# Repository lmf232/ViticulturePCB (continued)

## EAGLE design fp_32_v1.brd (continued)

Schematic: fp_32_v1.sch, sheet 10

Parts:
C41, C71: 0.1uF; C0603
C42: 0.1uF0402; C0402
C72, C73: 2.2uF; C0603
R82, R83: 0 0402; R0402
R97: FERRITE; R0603
U$5: MINISMP_PE44970_THRUHOLE; MINISMP_PE44970_THRU_HOLE
U$46: CVCO55BE-1000-1500_VCO
U$47: PV36W502C01B00_5KTRIMMER
U$48: HEADER_0.1''_1X2

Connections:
+5V: U$47.1; also elsewhere on the board
GND: C41.2, C42.2, C71.2, C72.2, C73.2, U$5.GND1, U$5.GND2, U$5.GND3, U$5.GND4, U$46.P$1 (1_GND), U$46.P$3 (3_GND), U$46.P$4 (4_GND), U$46.P$5 (5_GND), U$46.P$6 (6_GND), U$46.P$7 (7_GND), U$46.P$8 (8_GND), U$46.P$9 (9_GND), U$46.P$11 (11_GND), U$46.P$12 (12_GND), U$46.P$13 (13_GND), U$46.P$15 (15_GND), U$46.P$16 (16_GND), U$47.3, U$48.2; also elsewhere on the board
unnamed: C42.1, U$46.P$2 (2_VT), U$47.2, U$48.1
unnamed: R82.1, R83.2, U$46.P$10 (10_RF_OUT)
unnamed: R83.1, U$5.SIG
unnamed: C41.1, C73.1, R97.1, U$46.P$14 (14_VCC)
RF_SOURCE: R82.2; also elsewhere on the board
V+3V: C71.1, C72.1, R97.2; also elsewhere on the board

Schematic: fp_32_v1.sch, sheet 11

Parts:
C43: 100pF; C0603
C44: 1uF; C0603
C45, C46: 100pF/0402; C0402
R79, R84, R93, R94, R101, R102: 0 0402; R0402
R85: 100nH; R0603
R86: 22; R0805
U$1, U$3: MINISMP_PE44970_THRUHOLE; MINISMP_PE44970_THRU_HOLE
U$40: RF3378_AMPLIFIER; TO243AA/SOT89

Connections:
+5V: C43.1, C44.1, R86.2; also elsewhere on the board
GND: C43.2, C44.2, U$1.GND1, U$1.GND2, U$1.GND3, U$1.GND4, U$3.GND1, U$3.GND2, U$3.GND3, U$3.GND4, U$40.P2 (2_GND), U$40.P4 (4_GND); also elsewhere on the board
unnamed: R94.2, U$1.SIG
unnamed: R84.1, U$3.SIG
unnamed: C45.1, R85.1, U$40.P3 (3_RFOUT)
unnamed: R85.2, R86.1
unnamed: C46.2, U$40.P1 (1_RFIN)
unnamed: C45.2, R93.1, R94.1, R102.1
unnamed: C46.1, R79.2
unnamed: R101.2, R102.2
RF_TX: R93.2; also elsewhere on the board
TX_SWITCH_OUT: R79.1, R84.2, R101.1; also elsewhere on the board

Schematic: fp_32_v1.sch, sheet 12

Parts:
C47, C50, C75: 100pF; C0402
C48: 6.8nH; C0402
C49: 0.1uF0402; C0402
C74: 10pF; C0402
C76: 1000pF; C0402
R87: 0 0402; R0402
R88, R89, R90: 10k0402; R0402
U$42: LTC_5564_ENV_DET; QFN16
U$43: PV36W502C01B00_5KTRIMMER
U$50: HEADER_0.1''_1X2
U$51, U$52: HEADER_0.1''_1X3
U$53: SMA_CONN_SIDE

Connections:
+5V: C74.1, C75.1, C76.1, U$42.P$11 (11_VCCP), U$42.P$12 (12_VCCA), U$42.P$15 (15_VCCRF), U$43.1, U$51.1, U$52.1; also elsewhere on the board
GND: C48.2, C49.2, C50.2, C74.2, C75.2, C76.2, R88.1, R89.1, R90.1, U$42.EP (EP_GND), U$42.P$3 (3_GND), U$42.P$4 (4_GND), U$43.3, U$50.2, U$51.3, U$52.3, U$53.GND1, U$53.GND2; also elsewhere on the board
unnamed: C47.2, U$42.P$1 (1_RFIN)
unnamed: C49.1, R87.2, U$42.P$6 (6_VOUTADJ), U$50.1
unnamed: R87.1, U$43.2
unnamed: C50.1, U$42.P$14 (14_VREF)
unnamed: R88.2, U$42.P$8 (8_G1), U$51.2
unnamed: R89.2, U$42.P$7 (7_G0), U$52.2
unnamed: R90.2, U$42.P$5 (5_LEN)
unnamed: U$42.P$10 (10_VOUT), U$53.CENTER (A)
RX_AMP_OUT: C47.1, C48.1; also elsewhere on the board

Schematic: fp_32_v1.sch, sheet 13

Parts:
C51, C55, C59, C62, C67: 100uF; CAP_POL_RADIAL_8MM_3P5MMPAD
C52, C56, C60, C63, C68: 2.2uF; C0603
C53, C57, C61, C64, C69: 10uF; C1206
C54, C58, C65, C66, C70: 0.1uF; C0603
U$11, U$45, U$55, U$56, U$57, U$58, U$59: DELTRON_BANANA

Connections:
+3V3: C55.PIN+, C56.1, C57.1, C58.1, U$57.A, U$57.B; also elsewhere on the board
+5V: C51.PIN+, C52.1, C53.1, C54.1, U$56.A, U$56.B; also elsewhere on the board
-5V: C62.PIN-, C63.2, C64.2, C65.2, U$45.A, U$45.B; also elsewhere on the board
GND: C51.PIN-, C52.2, C53.2, C54.2, C55.PIN-, C56.2, C57.2, C58.2, C59.PIN-, C60.2, C61.2, C62.PIN+, C63.1, C64.1, C65.1, C66.2, C67.PIN-, C68.2, C69.2, C70.2, U$11.A, U$11.B, U$55.A, U$55.B; also elsewhere on the board
V+3V: C67.PIN+, C68.1, C69.1, C70.1, U$59.A, U$59.B; also elsewhere on the board
V_2P5: C59.PIN+, C60.1, C61.1, C66.1, U$58.A, U$58.B; also elsewhere on the board

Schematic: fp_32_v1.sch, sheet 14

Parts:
U$4: VHDCI_DIGILENT_V1; VHCDI_DIGILENT_V1

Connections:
A0_3_1: U$4.P29; also elsewhere on the board
A1_3_1: U$4.P31; also elsewhere on the board
CDRIVE: U$4.P34; also elsewhere on the board
CS1: U$4.P35; also elsewhere on the board
CS2: U$4.P37; also elsewhere on the board
CS3: U$4.P38; also elsewhere on the board
CS4: U$4.P40; also elsewhere on the board
CS5: U$4.P41; also elsewhere on the board
CS6: U$4.P43; also elsewhere on the board
CS7: U$4.P44; also elsewhere on the board
CS8: U$4.P46; also elsewhere on the board
CS9: U$4.P47; also elsewhere on the board
ENB_3_1: U$4.P28; also elsewhere on the board
F_A0_1A: U$4.P7; also elsewhere on the board
F_A0_1B: U$4.P12; also elsewhere on the board
F_A0_2: U$4.P23; also elsewhere on the board
F_A1_1A: U$4.P9; also elsewhere on the board
F_A1_1B: U$4.P13; also elsewhere on the board
F_A1_2: U$4.P25; also elsewhere on the board
F_ENB_1A: U$4.P6; also elsewhere on the board
F_ENB_1B: U$4.P10; also elsewhere on the board
F_ENB_2: U$4.P22; also elsewhere on the board
GND: U$4.G1, U$4.G2, U$4.G3, U$4.G4, U$4.P2, U$4.P5, U$4.P8, U$4.P11, U$4.P14, U$4.P21, U$4.P24, U$4.P27, U$4.P30, U$4.P33, U$4.P36, U$4.P39, U$4.P42, U$4.P45, U$4.P48, U$4.P55, U$4.P58, U$4.P61, U$4.P64, U$4.P67; also elsewhere on the board
MOSI: U$4.P3; also elsewhere on the board
NC1: U$4.P26
NC5: U$4.P32
NC6: U$4.P66
NC7: U$4.P65
NC8: U$4.P63
NC9: U$4.P62
NC10: U$4.P60
NC11: U$4.P59
NC12: U$4.P57
NC13: U$4.P56
RESETB: U$4.P1; also elsewhere on the board
SCK: U$4.P4; also elsewhere on the board
TX_PULSE: U$4.P68; also elsewhere on the board

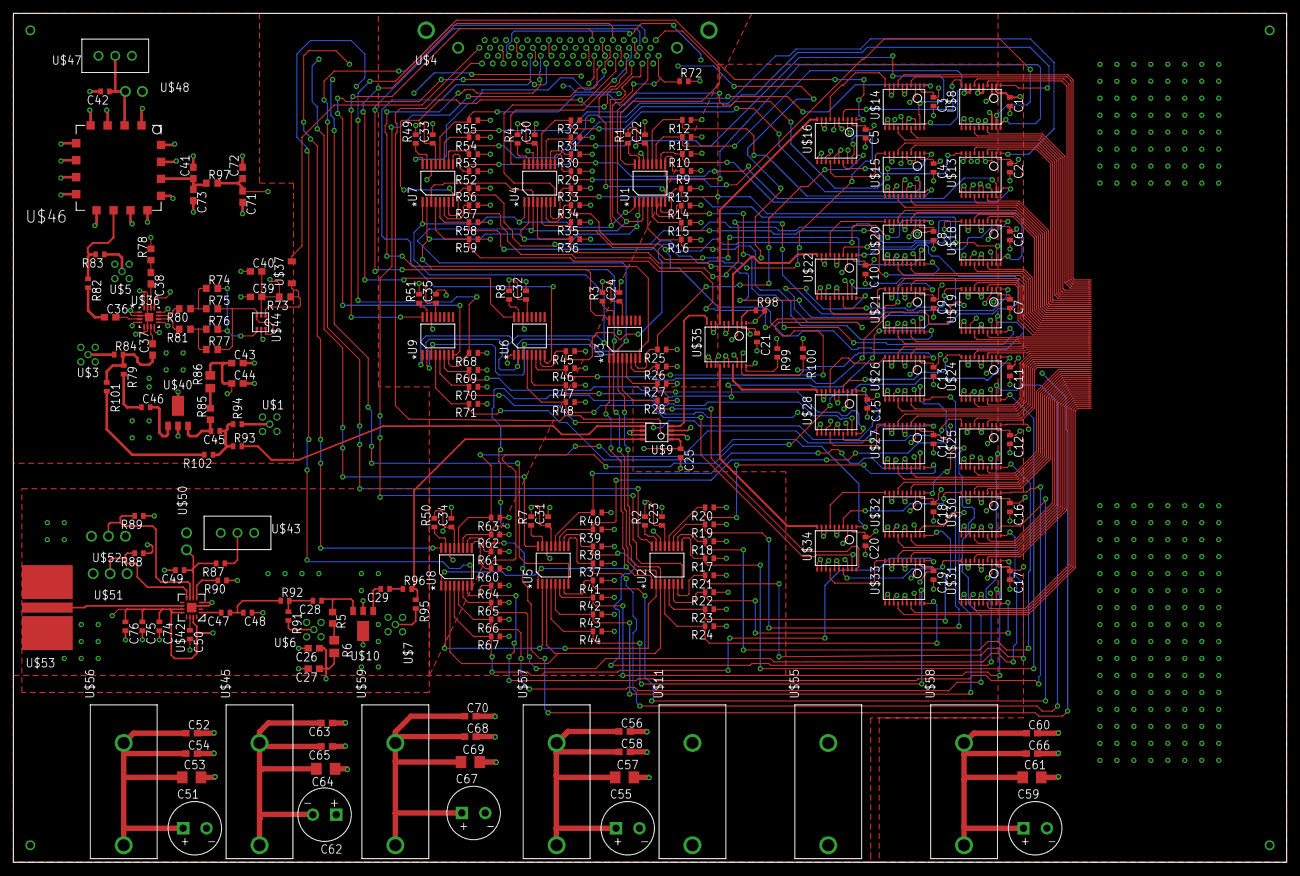
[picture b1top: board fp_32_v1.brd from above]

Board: 4 copper layers, 190.5 x 127.0 mm, 240 parts (0 on the bottom side), 229 nets.

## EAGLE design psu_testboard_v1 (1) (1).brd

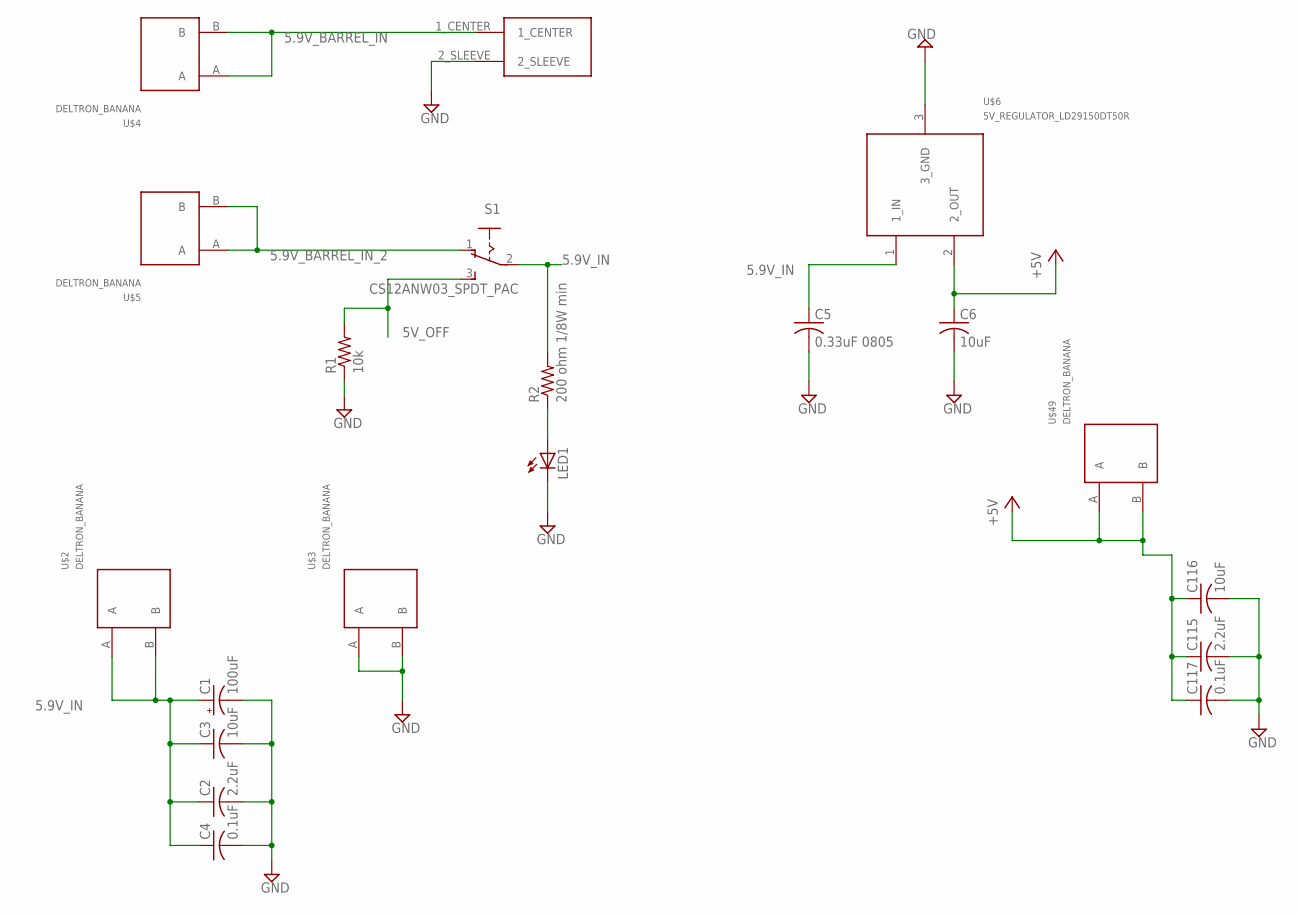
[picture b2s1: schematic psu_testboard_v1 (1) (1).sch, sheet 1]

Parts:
C1: 100uF; CAP_POL_RADIAL_8MM_3P5MMPAD
C2, C115: 2.2uF; C0603
C3, C116: 10uF; C1206
C4, C117: 0.1uF; C0603
C5: 0.33uF 0805; C0805
C6: 10uF; 5MM_SMT_ELECTROLYTICCAP_PANASONIC
LED1: LED3MM
R1: 10k; R0603
R2: 200 ohm 1/8W min; R0603
S1: CS12ANW03_SPDT_PAC; CS12ANW03_NKK_SPDT_SLIDESWITCH_PAC
U$1: BARREL_JACK_PJ-037A
U$2, U$3, U$4, U$5, U$49: DELTRON_BANANA
U$6: 5V_REGULATOR_LD29150DT50R; DPAK

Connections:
5.9V_BARREL_IN: U$1.1_CENTER, U$4.A, U$4.B
5.9V_BARREL_IN_2: S1.1, U$5.A, U$5.B
5.9V_IN: C1.PIN+, C2.1, C3.1, C4.1, C5.1, R2.2, S1.2, U$2.A, U$2.B, U$6.1 (1_IN); also elsewhere on the board
5V_OFF: R1.2, S1.3
+5V: C6.1+ (1), C115.1, C116.1, C117.1, U$6.2 (2_OUT), U$49.A, U$49.B; also elsewhere on the board
GND: C1.PIN-, C2.2, C3.2, C4.2, C5.2, C6.2- (2), C115.2, C116.2, C117.2, LED1.K (C), R1.1, U$1.2_SLEEVE, U$3.A, U$3.B, U$6.3 (3_GND); also elsewhere on the board
unnamed: LED1.A, R2.1

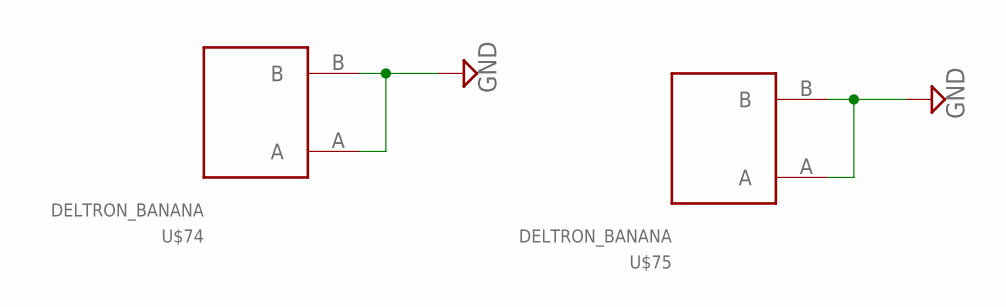
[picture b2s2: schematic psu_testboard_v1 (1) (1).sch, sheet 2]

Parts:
U$74, U$75: DELTRON_BANANA

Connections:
GND: U$74.A, U$74.B, U$75.A, U$75.B; also elsewhere on the board

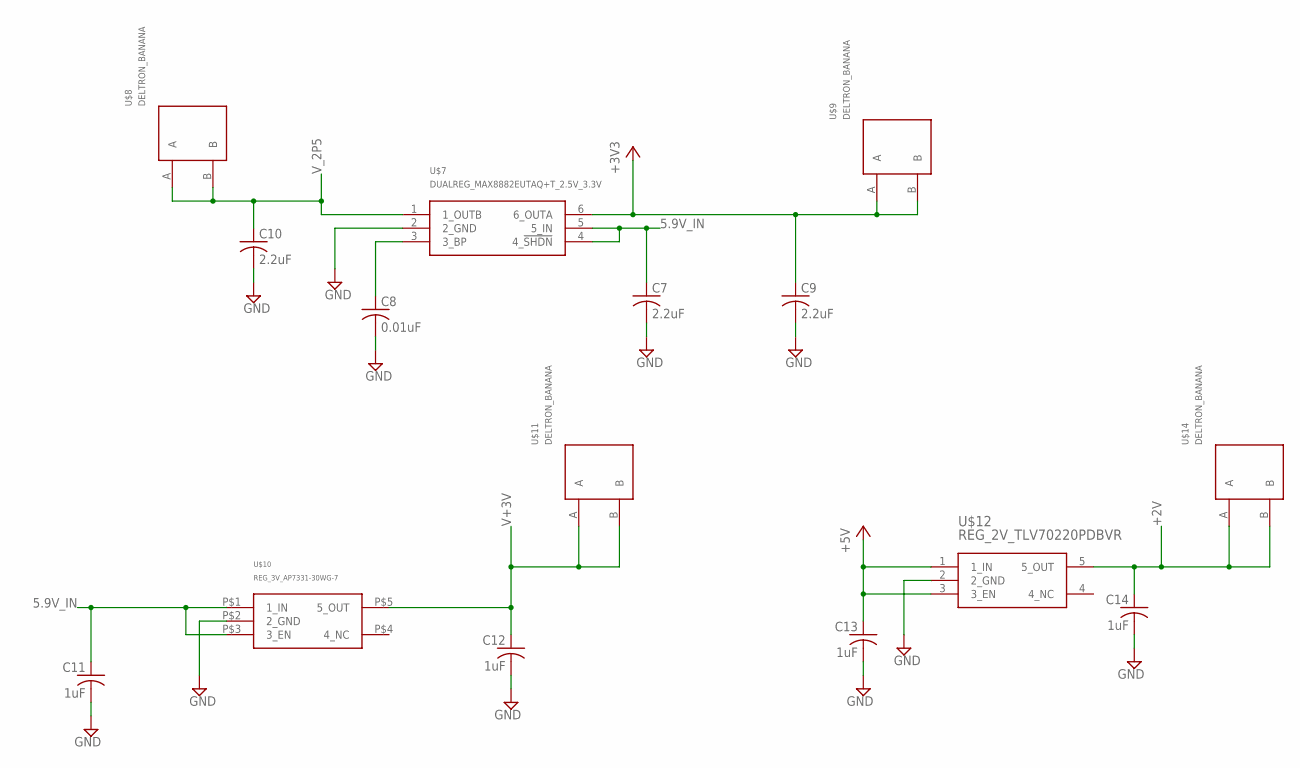
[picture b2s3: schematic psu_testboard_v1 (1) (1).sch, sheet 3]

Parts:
C7, C9, C10: 2.2uF; C0603
C8: 0.01uF; C0603
C11, C12, C13, C14: 1uF; C0603
U$7: DUALREG_MAX8882EUTAQ+T_2.5V_3.3V; SOT23-6
U$8, U$9, U$11, U$14: DELTRON_BANANA
U$10: REG_3V_AP7331-30WG-7; SOT-25
U$12: REG_2V_TLV70220PDBVR; SOT23-5

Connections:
5.9V_IN: C7.1, C11.1, U$7.4 (4_!SHDN), U$7.5 (5_IN), U$10.P$1 (1_IN), U$10.P$3 (3_EN); also elsewhere on the board
+2V: C14.1, U$12.5 (5_OUT), U$14.A, U$14.B
+3V3: C9.1, U$7.6 (6_OUTA), U$9.A, U$9.B; also elsewhere on the board
+5V: C13.1, U$12.1 (1_IN), U$12.3 (3_EN); also elsewhere on the board
GND: C7.2, C8.2, C9.2, C10.2, C11.2, C12.2, C13.2, C14.2, U$7.2 (2_GND), U$10.P$2 (2_GND), U$12.2 (2_GND); also elsewhere on the board
unnamed: C8.1, U$7.3 (3_BP)
V+3V: C12.1, U$10.P$5 (5_OUT), U$11.A, U$11.B
V_2P5: C10.1, U$7.1 (1_OUTB), U$8.A, U$8.B

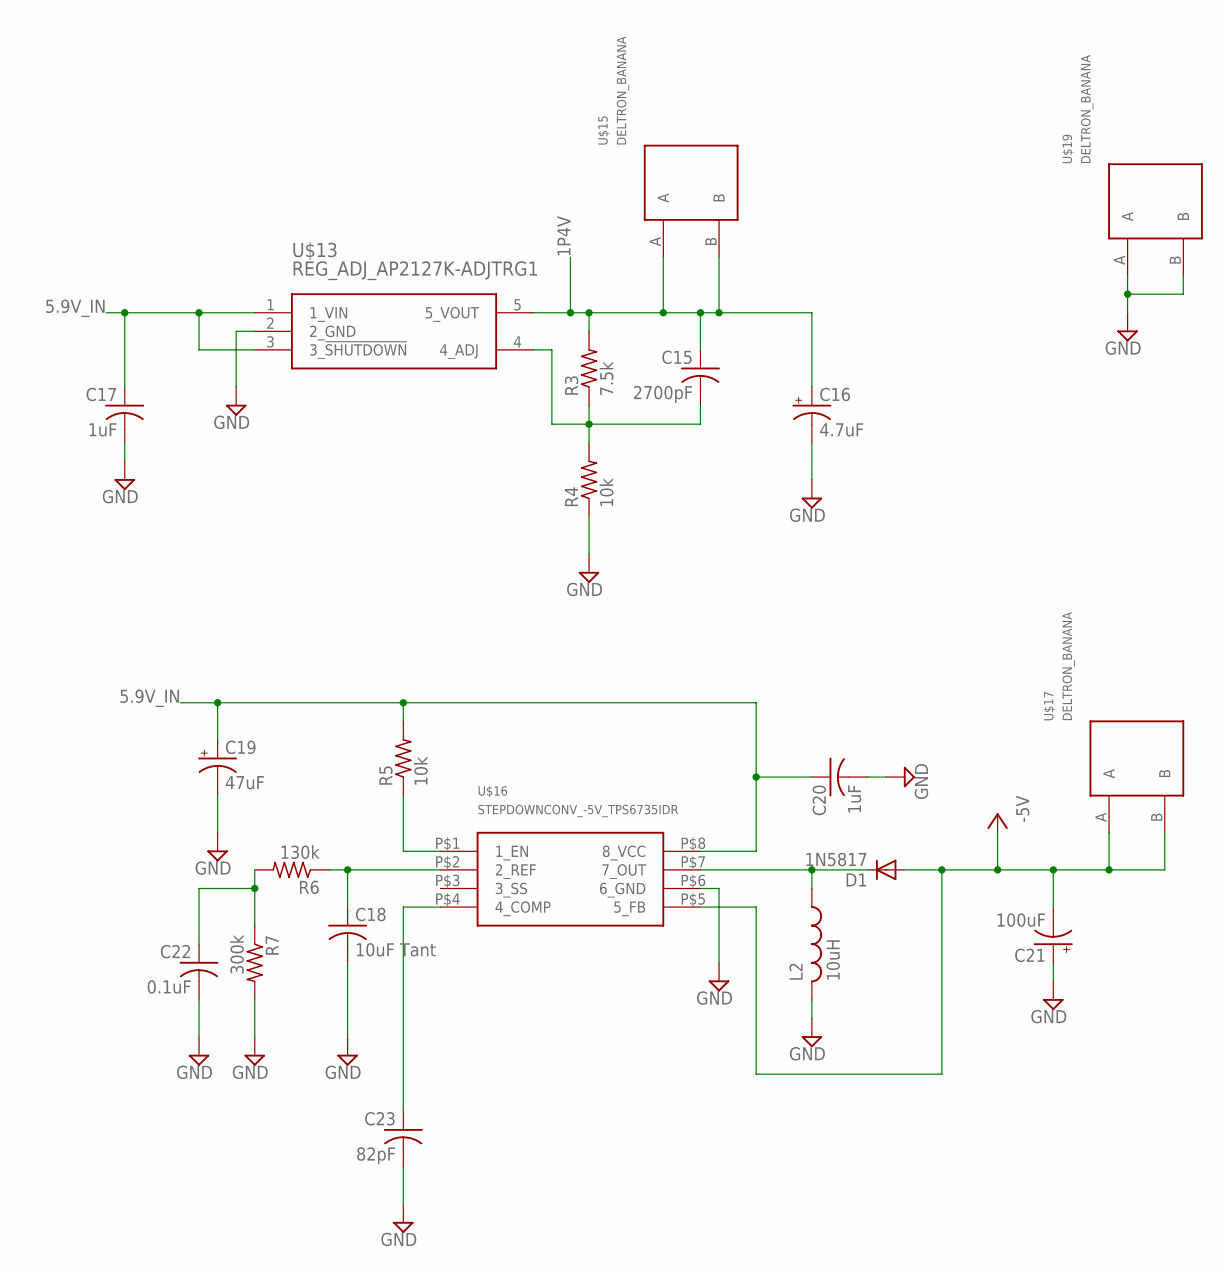
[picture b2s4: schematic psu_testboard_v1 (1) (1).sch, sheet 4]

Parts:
C15: 2700pF; C0603
C16: 4.7uF; E2,5RE
C17, C20: 1uF; C0603
C18: 10uF Tant; C1206
C19: 47uF; E5-10,5
C21: 100uF; E2,5-7
C22: 0.1uF; C0603
C23: 82pF; C0603
D1: 1N5817; DIODE-1N4148
L2: 10uH; COILCRAFT_POWERIND_DO1608C-103MLB
R3: 7.5k; R0603
R4, R5: 10k; R0603
R6: 130k; R0603
R7: 300k; R0603
U$13: REG_ADJ_AP2127K-ADJTRG1; SOT23-5
U$15, U$17, U$19: DELTRON_BANANA
U$16: STEPDOWNCONV_-5V_TPS6735IDR; SOIC8

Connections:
1P4V: C15.1, C16.+, R3.2, U$13.5 (5_VOUT), U$15.A, U$15.B
5.9V_IN: C17.1, C19.+, C20.1, R5.2, U$13.1 (1_VIN), U$13.3 (3_!SHUTDOWN), U$16.P$8 (8_VCC); also elsewhere on the board
-5V: C21.-, D1.A, U$16.P$5 (5_FB), U$17.A, U$17.B; also elsewhere on the board
GND: C16.-, C17.2, C18.2, C19.-, C20.2, C21.+, C22.2, C23.2, L2.P$2 (2), R4.1, R7.2, U$13.2 (2_GND), U$16.P$6 (6_GND), U$19.A, U$19.B; also elsewhere on the board
unnamed: D1.C, L2.P$1 (1), U$16.P$7 (7_OUT)
unnamed: C15.2, R3.1, R4.2, U$13.4 (4_ADJ)
unnamed: R5.1, U$16.P$1 (1_EN)
unnamed: C22.1, R6.2, R7.1
unnamed: C18.1, R6.1, U$16.P$2 (2_REF)
unnamed: C23.1, U$16.P$4 (4_COMP)

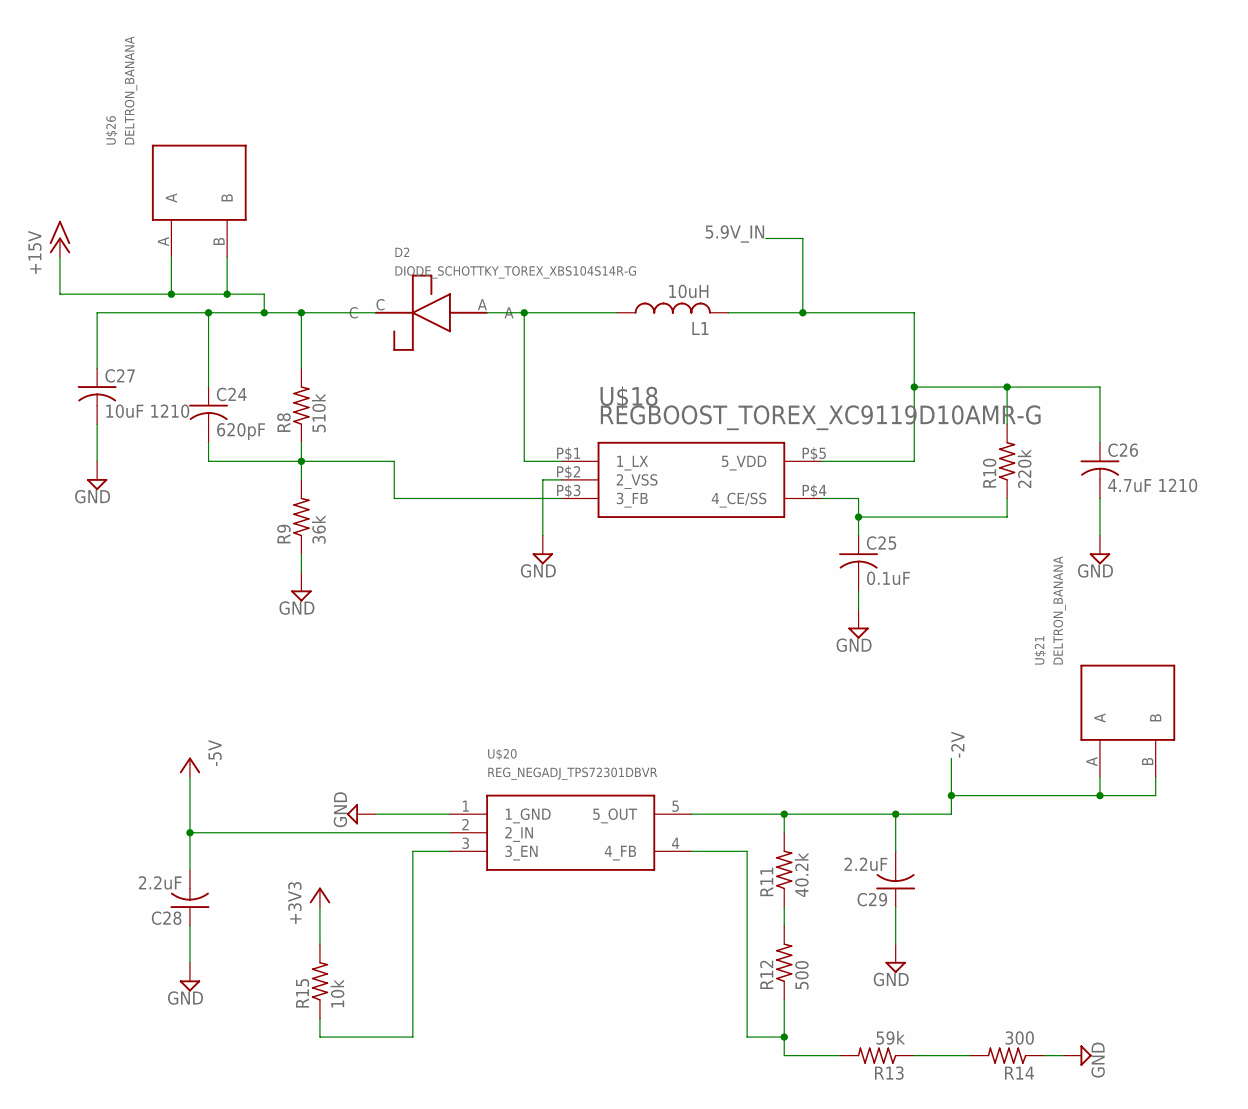
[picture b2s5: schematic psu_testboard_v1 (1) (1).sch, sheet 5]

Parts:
C24: 620pF; C0603
C25: 0.1uF; C0603
C26: 4.7uF 1210; C1210
C27: 10uF 1210; C1210
C28, C29: 2.2uF; C0603
D2: DIODE_SCHOTTKY_TOREX_XBS104S14R-G; SOD-123A
L1: 10uH; SUMIDA_INDUCTOR_CDRH4D18CNP-100PC
R8: 510k; R0603
R9: 36k; R0603
R10: 220k; R0603
R11: 40.2k; R0603
R12: 500; R0603
R13: 59k; R0603
R14: 300; R0603
R15: 10k; R0603
U$18: REGBOOST_TOREX_XC9119D10AMR-G; SOT25-5
U$20: REG_NEGADJ_TPS72301DBVR; SOT23-5
U$21, U$26: DELTRON_BANANA

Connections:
5.9V_IN: C26.1, L1.P$2 (2), R10.2, U$18.P$5 (5_VDD); also elsewhere on the board
+3V3: R15.2; also elsewhere on the board
+15V: C24.1, C27.1, D2.C, R8.2, U$26.A, U$26.B
-2V: C29.2, R11.2, U$20.5 (5_OUT), U$21.A, U$21.B
-5V: C28.2, U$20.2 (2_IN); also elsewhere on the board
GND: C25.2, C26.2, C27.2, C28.1, C29.1, R9.1, R14.1, U$18.P$2 (2_VSS), U$20.1 (1_GND); also elsewhere on the board
unnamed: R13.1, R14.2
unnamed: D2.A, L1.P$1 (1), U$18.P$1 (1_LX)
unnamed: C24.2, R8.1, R9.2, U$18.P$3 (3_FB)
unnamed: R12.1, R13.2, U$20.4 (4_FB)
unnamed: C25.1, R10.1, U$18.P$4 (4_CE/SS)
unnamed: R11.1, R12.2
unnamed: R15.1, U$20.3 (3_EN)

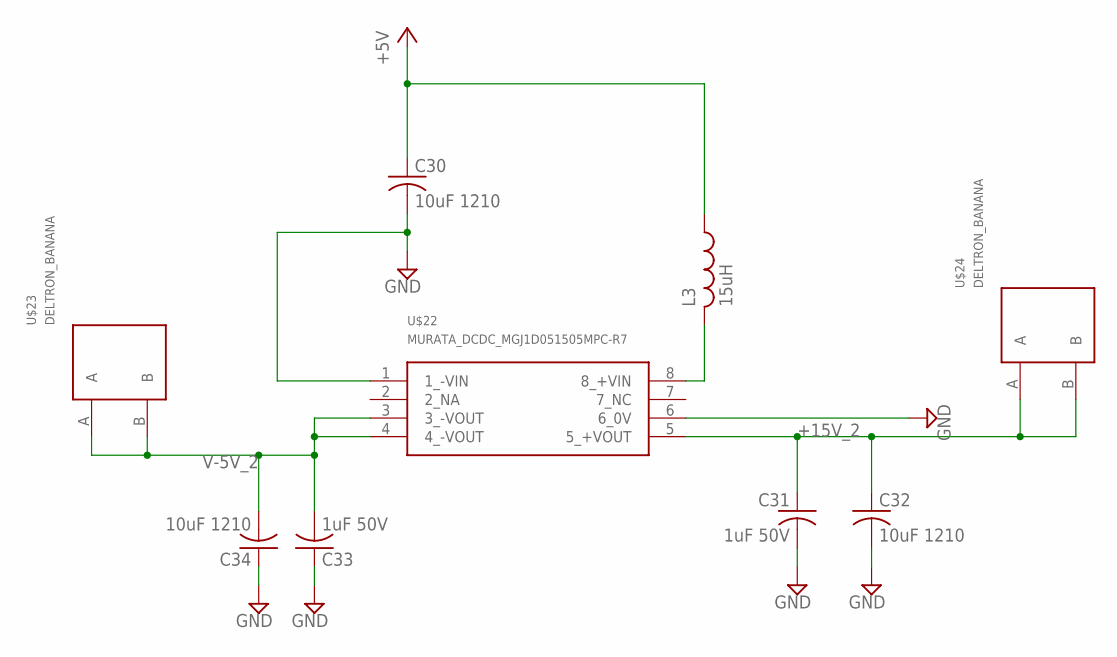
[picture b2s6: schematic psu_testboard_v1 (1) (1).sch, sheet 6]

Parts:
C30, C32, C34: 10uF 1210; C1210
C31, C33: 1uF 50V; C0603
L3: 15uH; 0207/5V
U$22: MURATA_DCDC_MGJ1D051505MPC-R7
U$23, U$24: DELTRON_BANANA

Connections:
+5V: C30.1, L3.1; also elsewhere on the board
+15V_2: C31.1, C32.1, U$22.5 (5_+VOUT), U$24.A, U$24.B
GND: C30.2, C31.2, C32.2, C33.1, C34.1, U$22.1 (1_-VIN), U$22.6 (6_0V); also elsewhere on the board
unnamed: L3.2, U$22.8 (8_+VIN)
V-5V_2: C33.2, C34.2, U$22.3 (3_-VOUT), U$22.4 (4_-VOUT), U$23.A, U$23.B

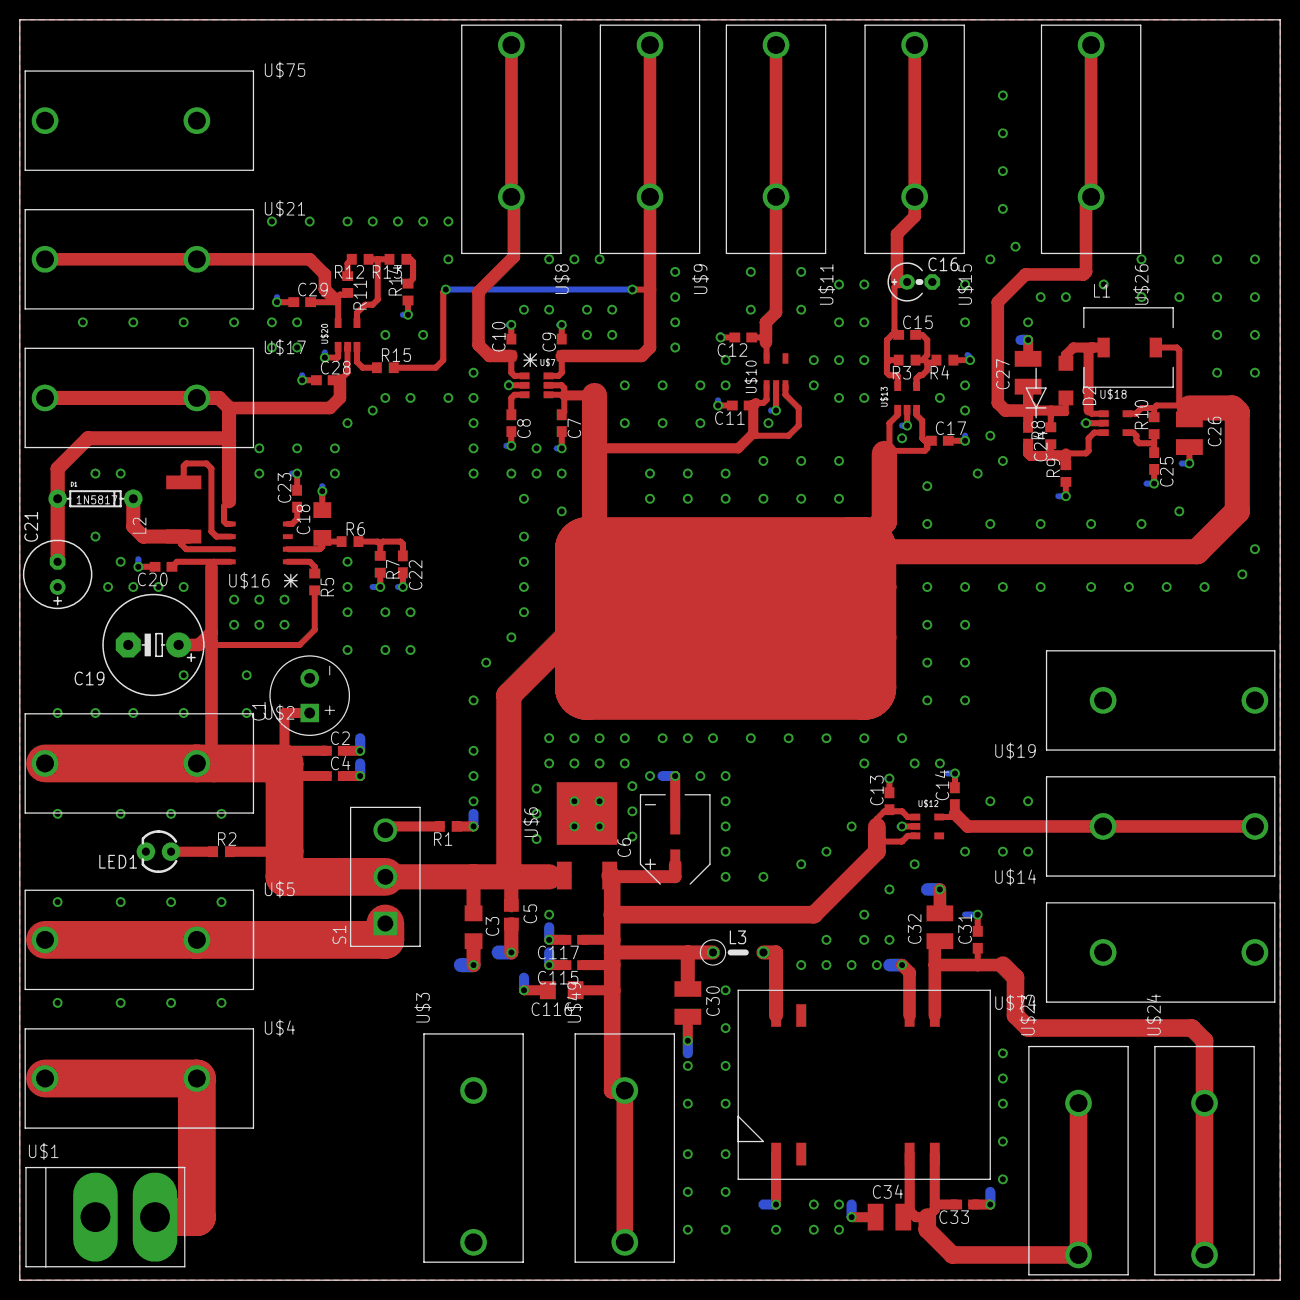
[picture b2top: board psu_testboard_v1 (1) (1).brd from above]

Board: 2 copper layers, 127.0 x 127.0 mm, 87 parts (0 on the bottom side), 32 nets.

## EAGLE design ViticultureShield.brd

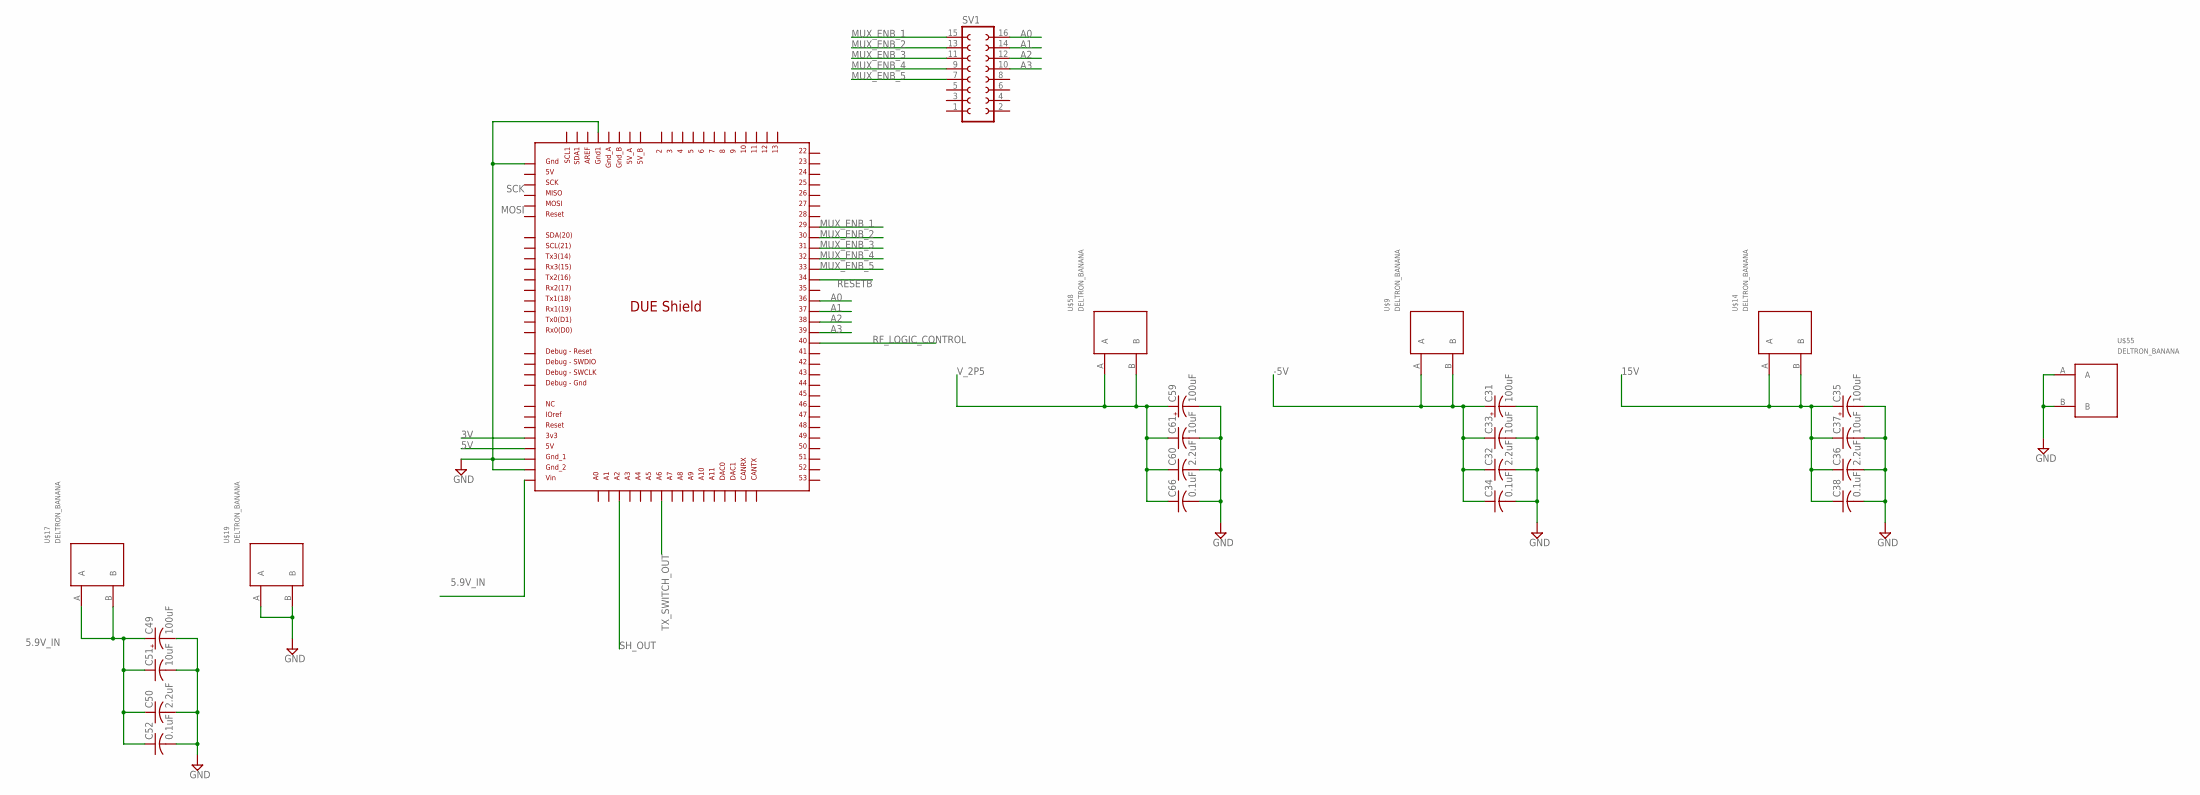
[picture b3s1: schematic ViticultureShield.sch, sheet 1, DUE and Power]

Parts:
C31, C35, C49, C59: 100uF; CAP_POL_RADIAL_8MM_3P5MMPAD
C32, C36, C50, C60: 2.2uF; C0603
C33, C37, C51, C61: 10uF; C1206
C34, C38, C52, C66: 0.1uF; C0603
SV1: FE08-2
U$1: DUE(NORMAL)
U$9, U$14, U$17, U$19, U$55, U$58: DELTRON_BANANA

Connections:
3V: U$1.3V3; also elsewhere on the board
5.9V_IN: C49.PIN+, C50.1, C51.1, C52.1, U$1.VIN, U$17.A, U$17.B
5V: U$1.5V; also elsewhere on the board
15V: C35.PIN+, C36.1, C37.1, C38.1, U$14.A, U$14.B; also elsewhere on the board
-5V: C31.PIN+, C32.1, C33.1, C34.1, U$9.A, U$9.B; also elsewhere on the board
A0: U$1.36; also elsewhere on the board
GND: C31.PIN-, C32.2, C33.2, C34.2, C35.PIN-, C36.2, C37.2, C38.2, C49.PIN-, C50.2, C51.2, C52.2, C59.PIN-, C60.2, C61.2, C66.2, U$1.5V_ICSP, U$1.GND1, U$1.GND_1, U$1.GND_2, U$19.A, U$19.B, U$55.A, U$55.B; also elsewhere on the board
MUX_ENB_1: SV1.15, U$1.29; also elsewhere on the board
MUX_ENB_2: SV1.13, U$1.30; also elsewhere on the board
MUX_ENB_3: SV1.11, U$1.31; also elsewhere on the board
MUX_ENB_4: SV1.9, U$1.32; also elsewhere on the board
MUX_ENB_5: SV1.7, U$1.33; also elsewhere on the board
RESETB: U$1.34
RF_LOGIC_CONTROL: U$1.40; also elsewhere on the board
SH_OUT: U$1.A2; also elsewhere on the board
TX_SWITCH_OUT: U$1.A6
V_2P5: C59.PIN+, C60.1, C61.1, C66.1, U$58.A, U$58.B; also elsewhere on the board

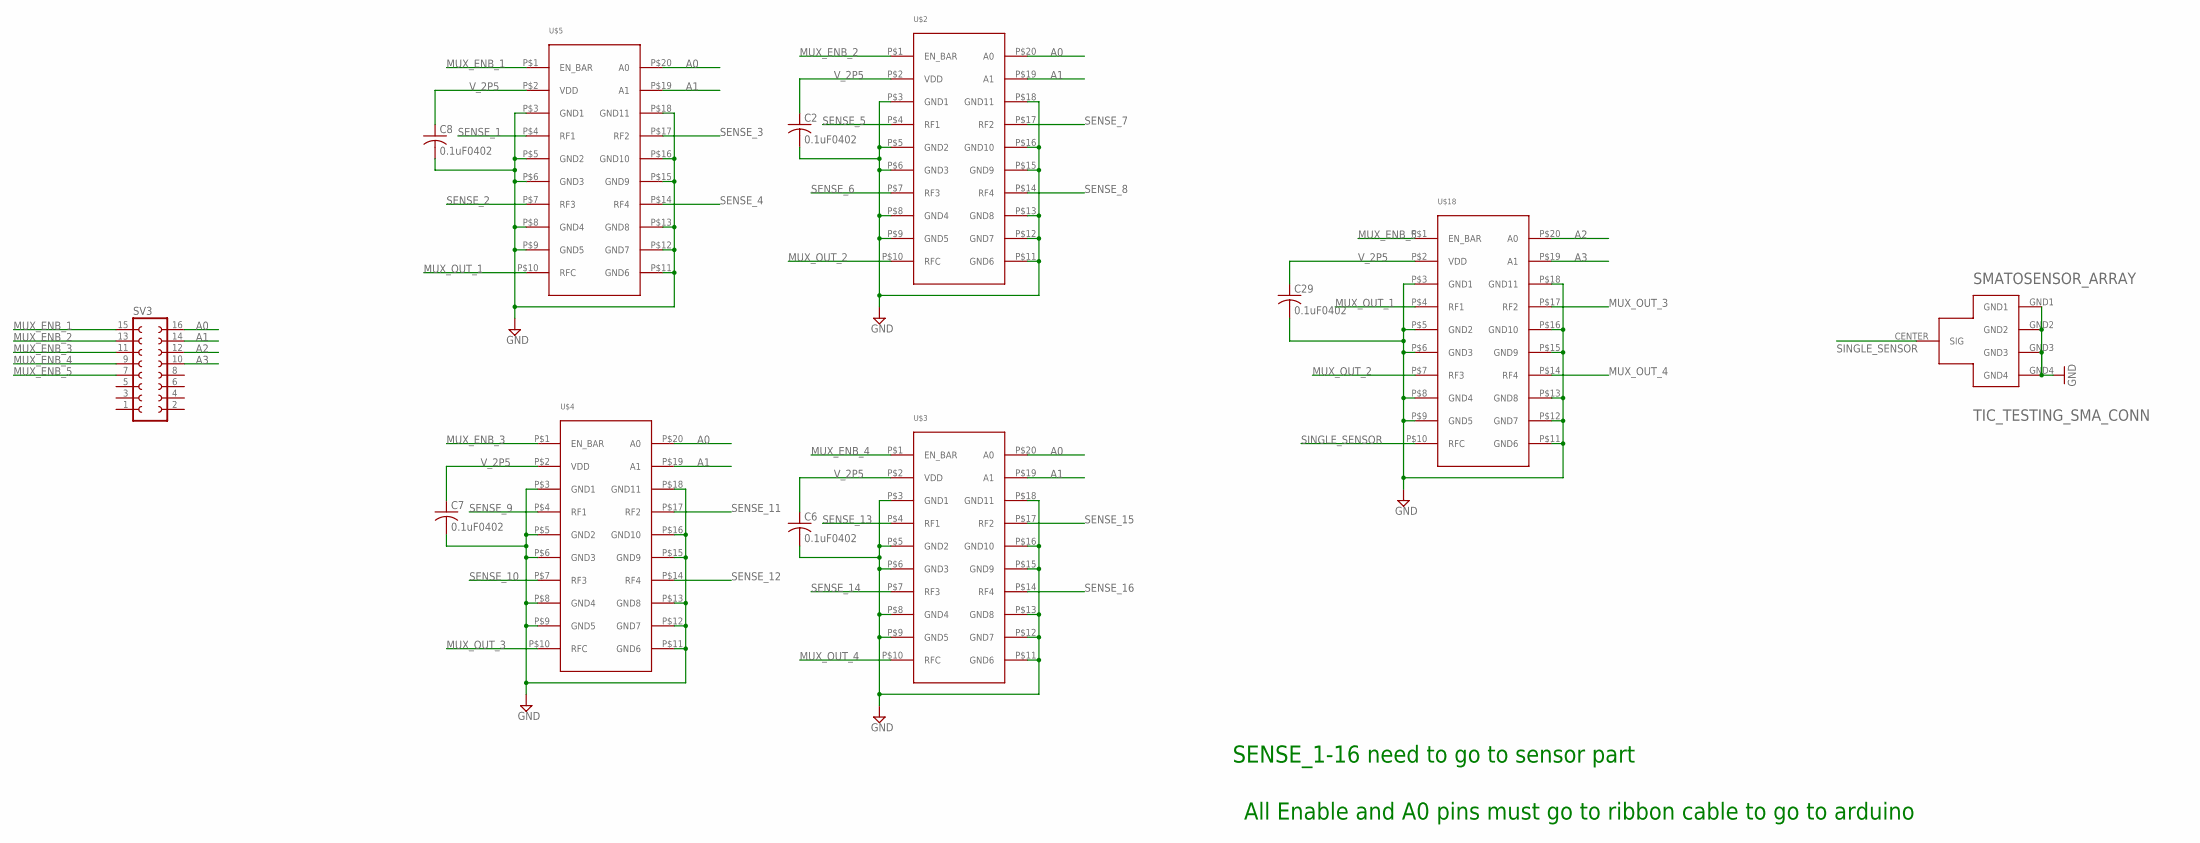
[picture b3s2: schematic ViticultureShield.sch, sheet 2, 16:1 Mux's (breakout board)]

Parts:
C2, C6, C7, C8, C29: 0.1uF0402; C0402
SMATOSENSOR_ARRAY: TIC_TESTING_SMA_CONN; TIC_TESTING_SMA_CONNECTOR_V1
SV3: FE08-2
U$2, U$3, U$4, U$5, U$18: TICLIB2_ADG904; TICLIB2_ADG904_TSSOP

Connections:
A0: SV3.16, U$2.P$20 (A0), U$3.P$20 (A0), U$4.P$20 (A0), U$5.P$20 (A0); also elsewhere on the board
A1: SV3.14, U$2.P$19 (A1), U$3.P$19 (A1), U$4.P$19 (A1), U$5.P$19 (A1)
A2: SV3.12, U$18.P$20 (A0)
A3: SV3.10, U$18.P$19 (A1)
GND: C2.2, C6.2, C7.2, C8.2, C29.2, SMATOSENSOR_ARRAY.GND1, SMATOSENSOR_ARRAY.GND2, SMATOSENSOR_ARRAY.GND3, SMATOSENSOR_ARRAY.GND4, U$2.P$3 (GND1), U$2.P$5 (GND2), U$2.P$6 (GND3), U$2.P$8 (GND4), U$2.P$9 (GND5), U$2.P$11 (GND6), U$2.P$12 (GND7), U$2.P$13 (GND8), U$2.P$15 (GND9), U$2.P$16 (GND10), U$2.P$18 (GND11), U$3.P$3 (GND1), U$3.P$5 (GND2), U$3.P$6 (GND3), U$3.P$8 (GND4), U$3.P$9 (GND5), U$3.P$11 (GND6), U$3.P$12 (GND7), U$3.P$13 (GND8), U$3.P$15 (GND9), U$3.P$16 (GND10), U$3.P$18 (GND11), U$4.P$3 (GND1), U$4.P$5 (GND2), U$4.P$6 (GND3), U$4.P$8 (GND4), U$4.P$9 (GND5), U$4.P$11 (GND6), U$4.P$12 (GND7), U$4.P$13 (GND8), U$4.P$15 (GND9), U$4.P$16 (GND10), U$4.P$18 (GND11), U$5.P$3 (GND1), U$5.P$5 (GND2), U$5.P$6 (GND3), U$5.P$8 (GND4), U$5.P$9 (GND5), U$5.P$11 (GND6), U$5.P$12 (GND7), U$5.P$13 (GND8), U$5.P$15 (GND9), U$5.P$16 (GND10), U$5.P$18 (GND11), U$18.P$3 (GND1), U$18.P$5 (GND2), U$18.P$6 (GND3), U$18.P$8 (GND4), U$18.P$9 (GND5), U$18.P$11 (GND6), U$18.P$12 (GND7), U$18.P$13 (GND8), U$18.P$15 (GND9), U$18.P$16 (GND10), U$18.P$18 (GND11); also elsewhere on the board
MUX_ENB_1: SV3.15, U$5.P$1 (EN_BAR); also elsewhere on the board
MUX_ENB_2: SV3.13, U$2.P$1 (EN_BAR); also elsewhere on the board
MUX_ENB_3: SV3.11, U$4.P$1 (EN_BAR); also elsewhere on the board
MUX_ENB_4: SV3.9, U$3.P$1 (EN_BAR); also elsewhere on the board
MUX_ENB_5: SV3.7, U$18.P$1 (EN_BAR); also elsewhere on the board
MUX_OUT_1: U$5.P$10 (RFC), U$18.P$4 (RF1)
MUX_OUT_2: U$2.P$10 (RFC), U$18.P$7 (RF3)
MUX_OUT_3: U$4.P$10 (RFC), U$18.P$17 (RF2)
MUX_OUT_4: U$3.P$10 (RFC), U$18.P$14 (RF4)
SENSE_1: U$5.P$4 (RF1)
SENSE_2: U$5.P$7 (RF3)
SENSE_3: U$5.P$17 (RF2)
SENSE_4: U$5.P$14 (RF4)
SENSE_5: U$2.P$4 (RF1)
SENSE_6: U$2.P$7 (RF3)
SENSE_7: U$2.P$17 (RF2)
SENSE_8: U$2.P$14 (RF4)
SENSE_9: U$4.P$4 (RF1)
SENSE_10: U$4.P$7 (RF3)
SENSE_11: U$4.P$17 (RF2)
SENSE_12: U$4.P$14 (RF4)
SENSE_13: U$3.P$4 (RF1)
SENSE_14: U$3.P$7 (RF3)
SENSE_15: U$3.P$17 (RF2)
SENSE_16: U$3.P$14 (RF4)
SINGLE_SENSOR: SMATOSENSOR_ARRAY.CENTER (SIG), U$18.P$10 (RFC)
V_2P5: C2.1, C6.1, C7.1, C8.1, C29.1, U$2.P$2 (VDD), U$3.P$2 (VDD), U$4.P$2 (VDD), U$5.P$2 (VDD), U$18.P$2 (VDD); also elsewhere on the board

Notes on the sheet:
SENSE_1-16 need to go to sensor part
All Enable and A0 pins must go to ribbon cable to go to arduino

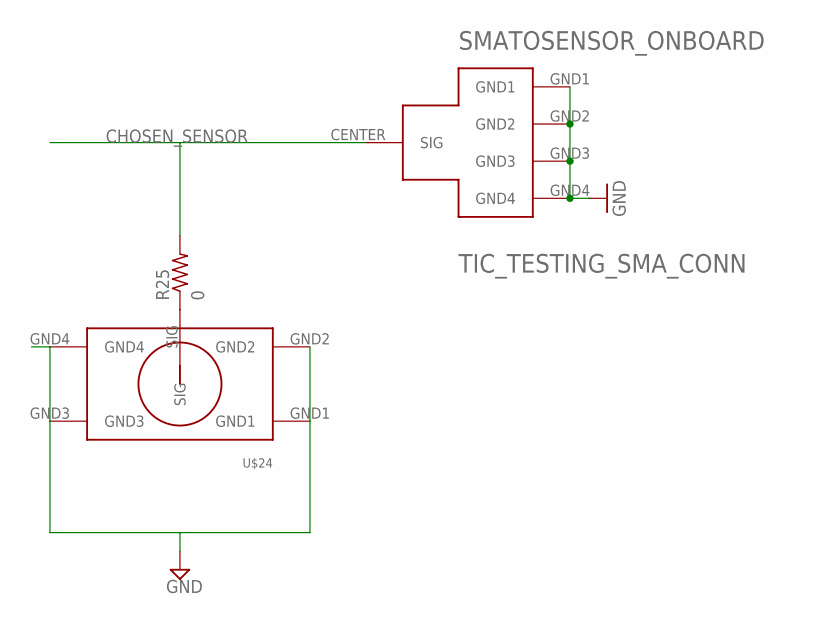
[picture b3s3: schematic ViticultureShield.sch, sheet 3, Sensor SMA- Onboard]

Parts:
R25: 0; R0603
SMATOSENSOR_ONBOARD: TIC_TESTING_SMA_CONN; TIC_TESTING_SMA_CONNECTOR_V1
U$24: MINISMP_PE44970_THRUHOLE; MINISMP_PE44970_THRU_HOLE

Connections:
CHOSEN_SENSOR: R25.2, SMATOSENSOR_ONBOARD.CENTER (SIG); also elsewhere on the board
GND: SMATOSENSOR_ONBOARD.GND1, SMATOSENSOR_ONBOARD.GND2, SMATOSENSOR_ONBOARD.GND3, SMATOSENSOR_ONBOARD.GND4, U$24.GND1, U$24.GND2, U$24.GND3; also elsewhere on the board
unnamed: R25.1, U$24.SIG
